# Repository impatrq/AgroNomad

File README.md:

<div align="center">
    
# [AgroNomad](https://linktr.ee/agronomad2026)

&nbsp;

| Página web | Linkedin | Instagram | Tiktok |
|------------|-------|-----------|---------|
|[AgroNomad Page](https://agro-nomad-page.vercel.app)|[AgroNomad](https://www.linkedin.com/company/145449198)|[@proyecto.agronomad](https://www.instagram.com/proyecto.agronomad/)|[@proyecto.agronomad](https://www.tiktok.com/@proyecto.agronomad)|

</div>

### MONITOREO INTELIGENTE DE GANADO 

AgroNomad es un sistema de monitoreo inteligente de ganado que combina collares smart, sensores, posicionamiento GPS y comunicación LoRa para obtener información de los animales directamente desde el campo.

El sistema está compuesto por collares inteligentes, una estación de recepción fija y una interfaz de usuario que permite visualizar y gestionar la información obtenida.

## Objetivo

Desarrollar un sistema IoT que permita realizar el seguimiento remoto del ganado, obteniendo información sobre su ubicación, movimiento y diferentes parámetros del animal, y centralizando estos datos en una estación de control.

## Componentes del Proyecto  

### AgroNeck

Collar inteligente colocado en el animal.

Se encarga de adquirir y procesar la información proveniente de los sensores y transmitirla mediante LoRa hacia el AgroBot.

### AgroBot

Estación de recepción fija del sistema.

Recibe la información enviada por los AgroNeck y funciona como centro de control para los animales monitoreados.

### AgroServer

Interfaz de usuario del sistema.

Permite visualizar y gestionar la información recibida desde los AgroNeck a través del AgroBot.

## Estructura del Proyecto  

| Ruta | Descripción |
|------------|---------|
|**docs**|Documentación e Informes del Proyecto|
|**firmware**|Software de los Microcontroladores y Aplicacion Web del Agrobot|
|**hardware**|Esquemáticos y PCB|
|**mechanical**|Diseños 3D|
|**web**|Landing Page del Proyecto|

---

<div align="center">

### AgroNeck  
<div style="margin-top:25px">

</div>

### AgroBot
<div style="margin-top:25px;">

</div>

</div>

## Equipo AgroNomad

<div align="center">
  
  <p><em>Equipo AgroNomad</em></p>
</div>

<br>

<div align="center">
  
  <p><em>Equipo AgroNomad en la Muestra Anual</em></p>
</div>

<br />

| Integrante | Rol | LinkedIn |
|------------|-----|----------|
| **Della Torre, Joaquín** | Diseño de placas electrónicas, montaje del AgroBot y desarrollo del AgroServer y Base de Datos. | [linkedin.com/in/joaquin-della-torre](https://www.linkedin.com/in/joaquin-della-torre/) |
| **Gonzalez Camiscia, Santiago** | Programación del AgroNeck, sistemas, optimización y gestión de energía con ESP32. | [linkedin.com/in/santiago-gonzalez](https://www.linkedin.com/in/santiago-gonzalez-a80209353/) |
| **Romero Dominguez, Braulio** | Diseño físico, desarrollo e integración del hardware y firmware y documentación. | [linkedin.com/in/braulio-romero-dominguez](www.linkedin.com/in/braulio-romero-dominguez-9a4729419) |
| **Villegas Gonzalez, Alejandro** | Desarrollo Web y de Interfaces. Programación e integración de datos. | [linkedin.com/in/alejandro-villegas-gonzalez](https://www.linkedin.com/in/alejandro-villegas-gonzalez-748a94432/) |

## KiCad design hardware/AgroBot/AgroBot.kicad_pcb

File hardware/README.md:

# Hardware

Esta carpeta contiene los diseños electrónicos del ecosistema AgroNomad desarrollados con KiCad. Incluye esquemáticos, placas PCB, proyectos de KiCad, vistas 3D y archivos de fabricación o impresión asociados a cada módulo.

El hardware se organiza en placas independientes según su función dentro del sistema:

- El **AgroBot** recibe los datos enviados por el AgroNeck.
- El **Cortex** constituye la lógica principal del collar AgroNeck.
- El **LoraShield**, el módulo MLX y el adaptador MOSFET son módulos auxiliares.
- El sistema **Solaria** administra la alimentación eléctrica mediante energía solar y baterías.

## Tipos de archivos

| Extensión | Descripción |
|---|---|
| `.kicad_sch` | Esquemático eléctrico: símbolos, conexiones y componentes de la placa. |
| `.kicad_pcb` | Diseño de la PCB: posición de componentes y trazado de pistas. |
| `.kicad_pro` | Archivo principal del proyecto de KiCad. |
| `.kicad_prl` | Configuración local de presentación o disposición del proyecto. |
| `*3D.png` | Vista renderizada del diseño tridimensional de la placa. |
| `*PCB.png` | Vista representativa del diseño o montaje de la PCB. |
| `fp-lib-table` / `sym-lib-table` | Tablas de bibliotecas locales de huellas y símbolos. |
| `libs/` | Bibliotecas, modelos 3D y recursos utilizados por el proyecto. |
| `gbr/` | Recursos relacionados con la preparación o trazado de fabricación. |

## Estructura

```text
hardware/
├── AgroBot/
├── Cortex/
├── LoraShield/
├── MLXModule/
├── MOSFETAdapter/
├── Solaria/
└── README.md
```

---

## AgroBot

El proyecto [`AgroBot/`](AgroBot/) corresponde a la estación de recepción fija del sistema.

**Función:** recibir la información emitida por los collares AgroNeck, determinar o conservar la ubicación mediante GPS y concentrar los datos para su procesamiento en el sistema principal.

<div align="center">
  
  <p><em>Diseño 3D del AgroBot</em></p>
</div>

El esquemático identifica una Raspberry Pi Zero 2 W como unidad de procesamiento, junto con módulos de comunicación LoRa y GPS.

| Archivo | Contenido |
|---|---|
| [`AgroBot.kicad_sch`](AgroBot/AgroBot.kicad_sch) | Esquemático del AgroBot. |
| [`AgroBot.kicad_pcb`](AgroBot/AgroBot.kicad_pcb) | Diseño físico y trazado de la PCB. |
| [`AgroBot.kicad_pro`](AgroBot/AgroBot.kicad_pro) | Proyecto de KiCad. |
| [`AgroBot3D.png`](AgroBot/AgroBot3D.png) | Representación tridimensional de la placa. |
| [`AgroBotPCB.png`](AgroBot/AgroBotPCB.png) | Vista de la PCB. |

---

## Cortex

El proyecto [`Cortex/`](Cortex/) representa la placa lógica principal del dispositivo AgroNeck, diseñado para instalarse dentro del collar inteligente.

**Función:** integrar el microcontrolador ESP32 con los módulos de comunicación y medición del collar. Procesa la información de posición y movimiento, comunica los datos por LoRa y gestiona las conexiones con los sensores.

<div align="center">
  
  <p><em>Diseño 3D de Cortex</em></p>
</div>

El esquemático contiene:

- ESP32 como unidad principal de procesamiento.
- Módulo GPS GY-NEO6MV2.
- Sensor MPU6050 para la detección de movimiento.
- Sensor MLX90614 para medición de temperatura.
- Interfaz de comunicación LoRa.
- Condensadores de desacoplo y conectores de alimentación o módulos auxiliares.

| Archivo | Contenido |
|---|---|
| [`Cortex.kicad_sch`](Cortex/Cortex.kicad_sch) | Esquemático de la lógica del AgroNeck. |
| [`Cortex.kicad_pcb`](Cortex/Cortex.kicad_pcb) | Diseño físico de la placa principal. |
| [`Cortex.kicad_pro`](Cortex/Cortex.kicad_pro) | Proyecto de KiCad. |
| [`Cortex3D.png`](Cortex/Cortex3D.png) | Vista tridimensional de Cortex. |
| [`CortexPCB.png`](Cortex/CortexPCB.png) | Vista de la PCB. |

---

## LoraShield

El proyecto [`LoraShield/`](LoraShield/) contiene una placa adaptadora basada en el módulo inalámbrico XL1278.

**Función:** proporcionar la interfaz física y eléctrica necesaria para conectar el módulo LoRa mediante conectores y facilitar su integración en el sistema.

<div align="center">
  
  <p><em>Diseño 3D del adaptador LoRa</em></p>
</div>

| Archivo | Contenido |
|---|---|
| [`LoraShield.kicad_sch`](LoraShield/LoraShield.kicad_sch) | Esquemático del adaptador LoRa. |
| [`LoraShield.kicad_pcb`](LoraShield/LoraShield.kicad_pcb) | Diseño físico de la placa. |
| [`LoraShield.kicad_pro`](LoraShield/LoraShield.kicad_pro) | Proyecto de KiCad. |
| [`LoraShield3D.png`](LoraShield/LoraShield3D.png) | Vista tridimensional del módulo. |
| [`LoraShieldPCB.png`](LoraShield/LoraShieldPCB.png) | Vista de la PCB. |

---

## MLXModule

El proyecto [`MLXModule/`](MLXModule/) corresponde a una placa auxiliar diseñada para el sensor infrarrojo de temperatura MLX90614.

**Función:** montar y conectar el sensor MLX90614 mediante un conector de cuatro posiciones, permitiendo llevar las señales de alimentación y comunicación entre el módulo y la placa Cortex.

<div align="center">
  
  <p><em>Módulo auxiliar del sensor MLX90614</em></p>
</div>

| Archivo | Contenido |
|---|---|
| [`MLXModule.kicad_sch`](MLXModule/MLXModule.kicad_sch) | Esquemático del módulo MLX90614. |
| [`MLXModule.kicad_pcb`](MLXModule/MLXModule.kicad_pcb) | Diseño físico de la placa auxiliar. |
| [`MLXModule.kicad_pro`](MLXModule/MLXModule.kicad_pro) | Proyecto de KiCad. |
| [`MLXModule3D.png`](MLXModule/MLXModule3D.png) | Vista tridimensional del módulo. |
| [`MLXModulePCB.png`](MLXModule/MLXModulePCB.png) | Vista de la PCB. |

---

## MOSFETAdapter

El proyecto [`MOSFETAdapter/`](MOSFETAdapter/) reúne un adaptador para trabajar con MOSFET en paquetes THT y SMD.

**Función:** facilitar el montaje y reemplazo de MOSFET en prototipos o placas donde se necesita compatibilidad entre formatos de componentes.

El diseño incluye los modelos **AO3401A** y **IRF9540N**, utilizados como dispositivos MOSFET en el proyecto.

| Archivo | Contenido |
|---|---|
| [`Adapter.kicad_sch`](MOSFETAdapter/Adapter.kicad_sch) | Esquemático del adaptador. |
| [`Adapter.kicad_pcb`](MOSFETAdapter/Adapter.kicad_pcb) | Diseño físico de la PCB. |
| [`Adapter.kicad_pro`](MOSFETAdapter/Adapter.kicad_pro) | Proyecto de KiCad. |
| [`Adapter3D.png`](MOSFETAdapter/Adapter3D.png) | Vista tridimensional del adaptador. |
| [`AdapterPCB.png`](MOSFETAdapter/AdapterPCB.png) | Vista de la PCB. |

---

## Solaria

El proyecto [`Solaria/`](Solaria/) corresponde al sistema electrónico de alimentación solar.

**Función:** administrar la energía captada por paneles solares, cargar baterías y elevar o distribuir la tensión necesaria para alimentar los dispositivos del sistema.

<div align="center">
  
  <p><em>Diseño 3D del sistema de alimentación</em></p>
</div>

El esquemático utiliza módulos TP4056 para la carga y gestión de baterías, junto con un conversor elevador MT3608 y MOSFET de potencia. La PCB incluye entradas y conexiones para panel solar, batería y carga.

| Archivo | Contenido |
|---|---|
| [`Solaria.kicad_sch`](Solaria/Solaria.kicad_sch) | Esquemático del sistema de alimentación. |
| [`Solaria.kicad_pcb`](Solaria/Solaria.kicad_pcb) | Diseño físico de la PCB. |
| [`Solaria.kicad_pro`](Solaria/Solaria.kicad_pro) | Proyecto de KiCad. |
| [`Solaria3D.png`](Solaria/Solaria3D.png) | Vista tridimensional de la placa. |
| [`SolariaPCB.png`](Solaria/SolariaPCB.png) | Vista de la PCB. |

## Abrir los diseños

1. Instalar una versión de KiCad compatible con los archivos del proyecto.
2. Abrir el archivo `.kicad_pro` correspondiente a la placa.
3. Desde el proyecto abrir `.kicad_sch` para revisar el circuito o `.kicad_pcb` para revisar el diseño físico.
4. Verificar las bibliotecas locales y los modelos 3D incluidos en `libs/` antes de modificar o exportar el diseño.

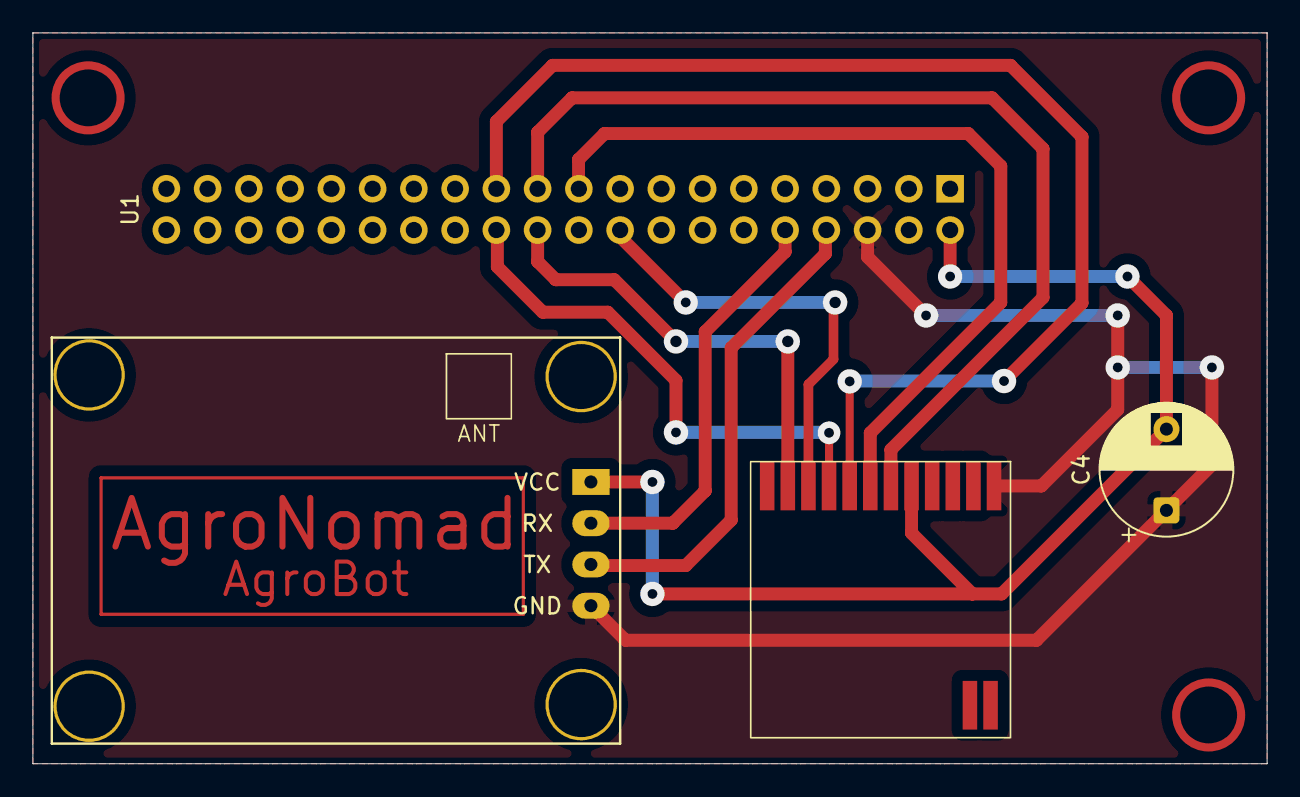
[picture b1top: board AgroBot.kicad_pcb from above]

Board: 2 copper layers, 76.0 x 45.0 mm, 4 parts (0 on the bottom side), 10 nets.

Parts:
C4: 100uF; CP_Radial_D8.0mm_P5.00mm
U1: Pi Zero 2 W; PinHeader_2x20_P2.54mm_Vertical
U2: XL1278
U3: GY-NEO6MV2

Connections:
GND: C4.1, U1.6 (GND), U2.1 (GND), U3.4 (GND)
GPS_RX: U1.10 (GPIO15), U3.2 (RX)
GPS_TX: U1.8 (GPIO14), U3.3 (TX)
LORA_CLK: U1.23 (GPIO11), U2.8 (SCLK)
LORA_CS: U1.24 (GPIO8), U2.9 (NSS)
LORA_DIO0: U1.18 (GPIO24), U2.10 (DIO0)
LORA_MISO: U1.21 (GPIO09), U2.6 (MISO)
LORA_MOSI: U1.19 (GPIO10), U2.7 (MOSI)
LORA_RESET: U1.22 (GPIO25), U2.11 (REST)
VCC: C4.2, U1.2 (+5V), U2.5 (VCC), U3.1 (VCC)

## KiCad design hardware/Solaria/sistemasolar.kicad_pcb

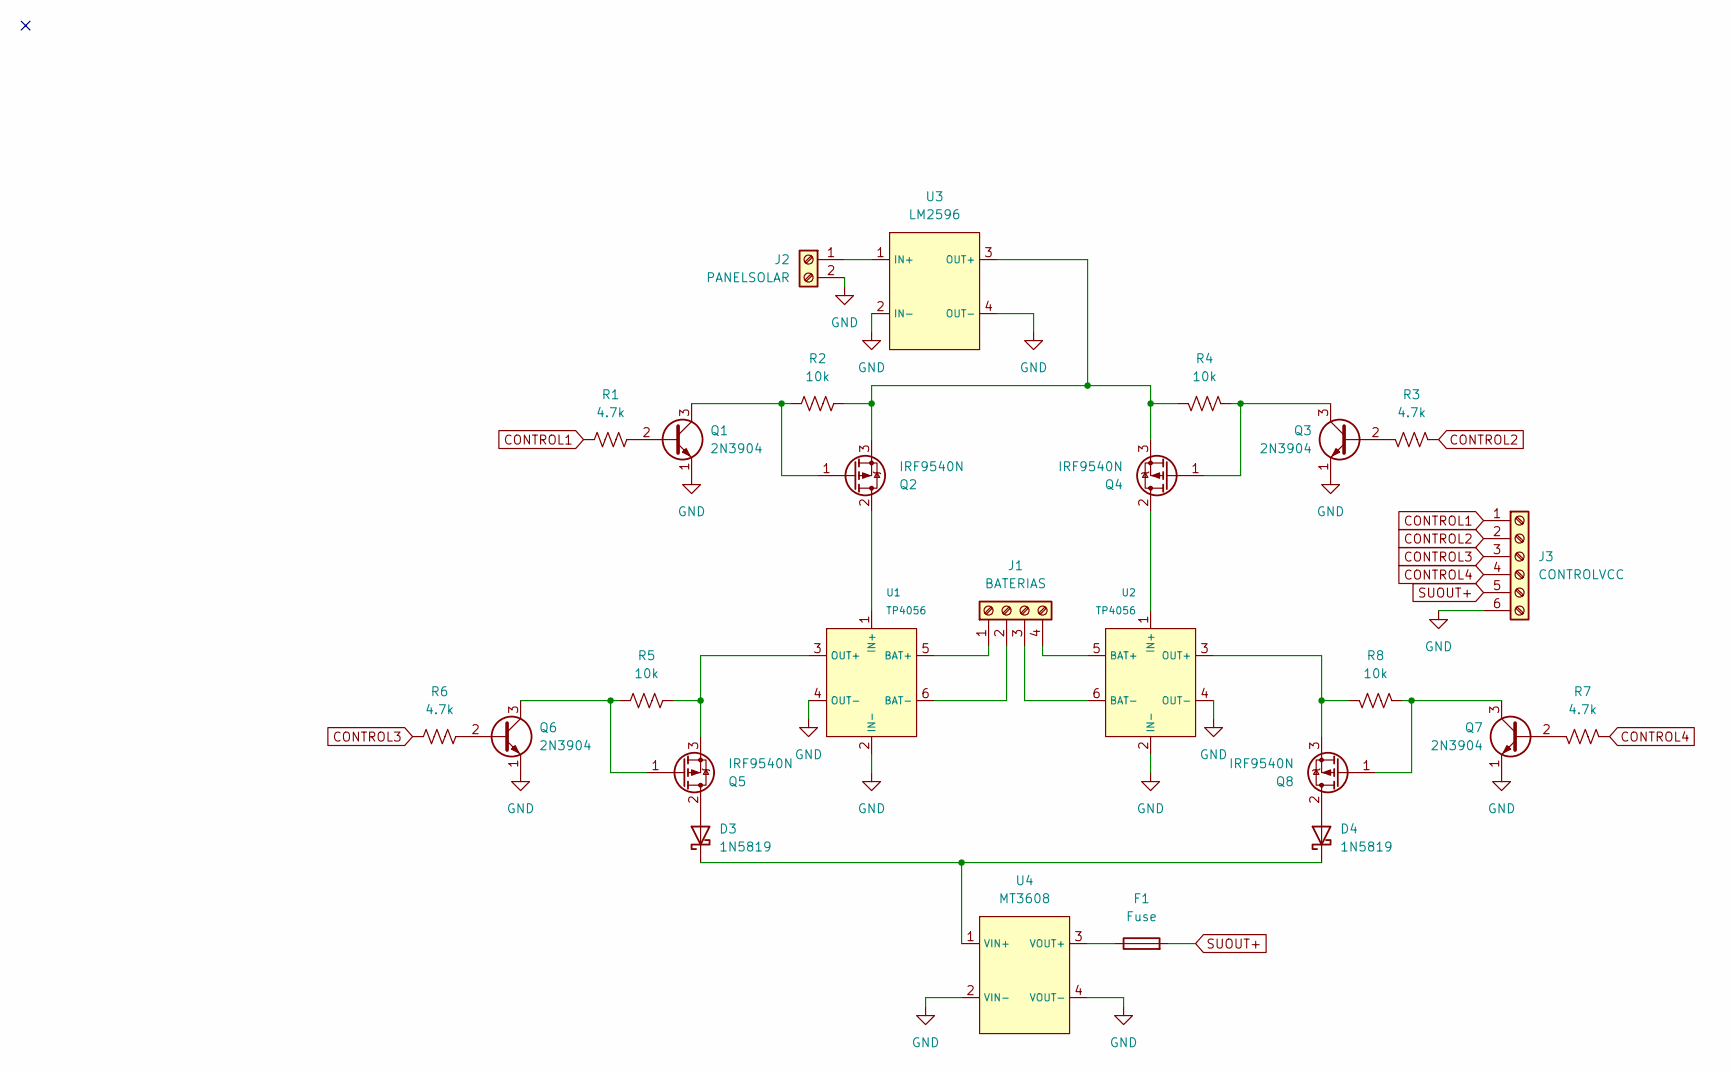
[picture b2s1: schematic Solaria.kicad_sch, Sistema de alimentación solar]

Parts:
D3, D4: 1N5819; D_DO-41_SOD81_P10.16mm_Horizontal
F1: Fuse; Fuseholder_Clip-5x20mm_Littelfuse_445-030_Inline_P20.50x5.2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
J1: BATERIAS; TerminalBlock_MaiXu_MX126-5.0-04P_1x04_P5.00mm
J2: PANELSOLAR; TerminalBlock_MaiXu_MX126-5.0-02P_1x02_P5.00mm
J3: CONTROLVCC; TerminalBlock_MaiXu_MX126-5.0-06P_1x06_P5.00mm
Q1, Q3, Q6, Q7: 2N3904; TO-92_Inline
Q2, Q4, Q5, Q8: IRF9540N; TO-220-3_Vertical
R1, R3, R6, R7: 4.7k; R_Axial_DIN0204_L3.6mm_D1.6mm_P7.62mm_Horizontal
R2, R4, R5, R8: 10k; R_Axial_DIN0204_L3.6mm_D1.6mm_P7.62mm_Horizontal
U1, U2: TP4056
U3: LM2596
U4: MT3608

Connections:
CONTROL1: J3.1, R1.1
CONTROL2: J3.2, R3.1
CONTROL3: J3.3, R6.1
CONTROL4: J3.4, R7.1
GND: J2.2, J3.6, Q1.1 (E), Q3.1 (E), Q6.1 (E), Q7.1 (E), U1.2 (IN-), U1.4 (OUT-), U2.2 (IN-), U2.4 (OUT-), U3.2 (IN-), U3.4 (OUT-), U4.2 (VIN-), U4.4 (VOUT-)
unnamed: D3.2 (A), Q5.2 (D)
unnamed: D3.1 (K), D4.1 (K), U4.1 (VIN+)
unnamed: D4.2 (A), Q8.2 (D)
unnamed: J1.1, U1.5 (BAT+)
unnamed: J1.2, U1.6 (BAT-)
unnamed: J1.3, U2.6 (BAT-)
unnamed: J1.4, U2.5 (BAT+)
unnamed: J2.1, U3.1 (IN+)
unnamed: Q1.2 (B), R1.2
unnamed: Q1.3 (C), Q2.1 (G), R2.1
unnamed: Q2.2 (D), U1.1 (IN+)
unnamed: Q2.3 (S), Q4.3 (S), R2.2, R4.2, U3.3 (OUT+)
unnamed: Q3.2 (B), R3.2
unnamed: Q3.3 (C), Q4.1 (G), R4.1
unnamed: Q4.2 (D), U2.1 (IN+)
unnamed: Q5.1 (G), Q6.3 (C), R5.1
unnamed: Q5.3 (S), R5.2, U1.3 (OUT+)
unnamed: Q6.2 (B), R6.2
unnamed: Q7.2 (B), R7.2
unnamed: Q7.3 (C), Q8.1 (G), R8.1
unnamed: Q8.3 (S), R8.2, U2.3 (OUT+)
unnamed: F1.1, U4.3 (VOUT+)
SUOUT+: F1.2, J3.5

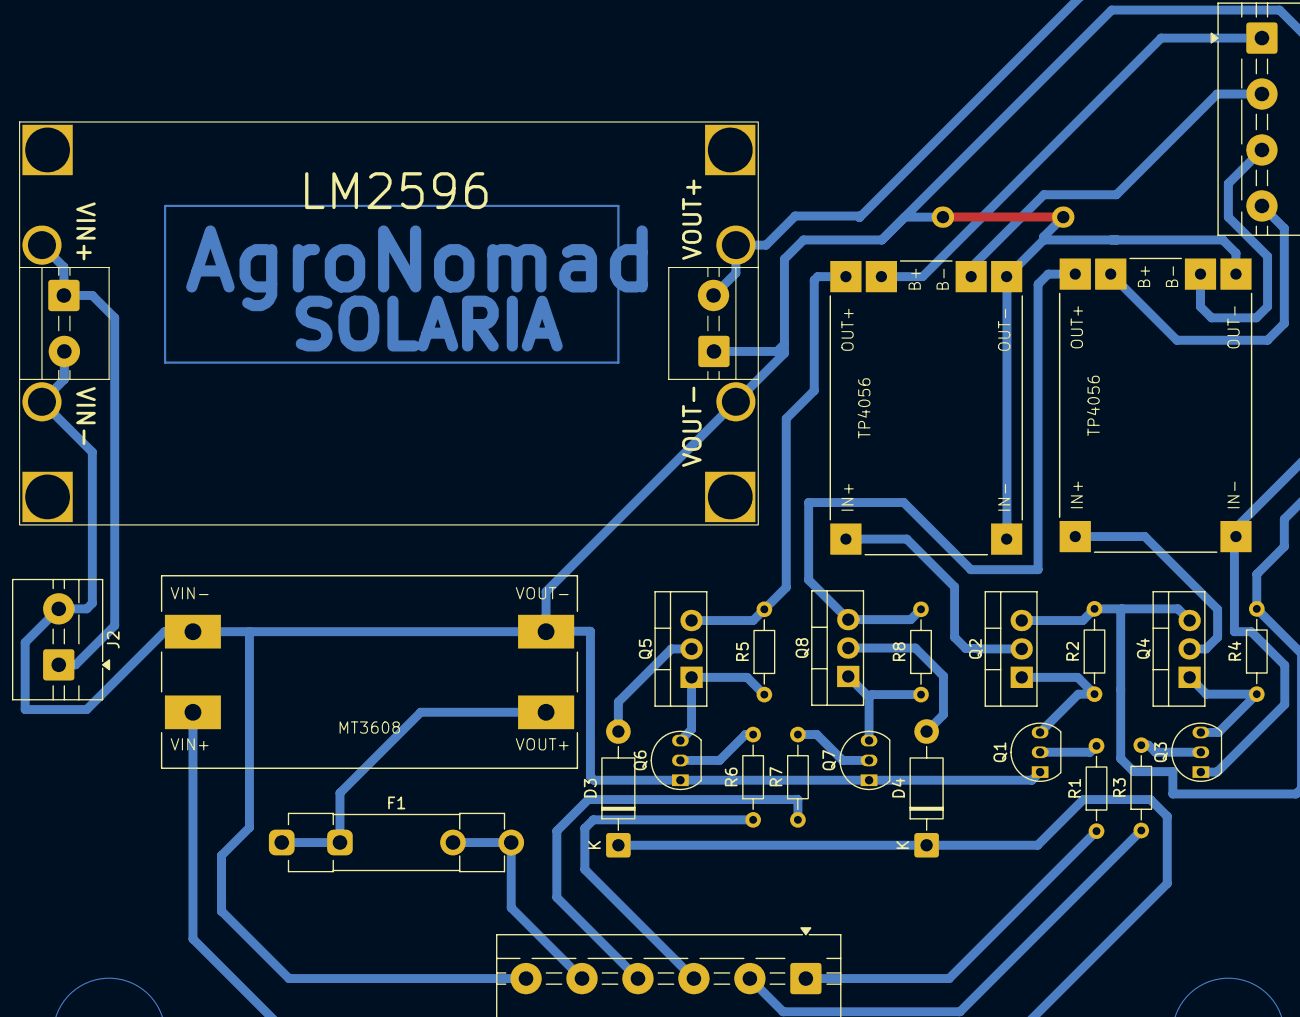
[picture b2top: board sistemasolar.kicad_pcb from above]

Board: 2 copper layers, 26 parts (0 on the bottom side), 28 nets.

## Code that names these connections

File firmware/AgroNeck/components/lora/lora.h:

#include <stdint.h>
#include <stdbool.h>

// Pines LORA
#define LORA_CS         5
#define LORA_RESET      14
#define LORA_CLK        18
#define LORA_MISO       19
#define LORA_MOSI       23
#define LORA_DIO0       10

// Estructuras
typedef struct __attribute__((packed)) {
    uint16_t id_collar;
    float temperatura;     
    int32_t latitud;       
    int32_t longitud;     
} payload_t;               

// Funciones
void lora_init(void);
void lora_reinit(void);
void transmitir_datos(payload_t *paquete);
uint8_t lora_version(void);   // diagnóstico: lee el registro de versión (0x42)

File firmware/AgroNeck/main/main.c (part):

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#define SEND_EVERYTIME 1

// CONTROL DE ALIMENTACIÓN - C1+C4 o C2+C3
#define MOSFET1 25 // GPIO del MOSFET CONTROL3
#define MOSFET2 26 // GPIO del MOSFET CONTROL4
#define MOSFET3 32 // GPIO del MOSFET CONTROL1
#define MOSFET4 33 // GPIO del MOSFET CONTROL2

// Mascara de manejo de los 4 pines
#define GPIO_MOSFET_MASK ((1ULL<<MOSFET1) | (1ULL<<MOSFET2) | (1ULL<<MOSFET3) | (1ULL<<MOSFET4))
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
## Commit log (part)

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2026-04-08 Anteproyecto uploaded
2026-04-08 docs readme updated
2026-04-08 created dir for docs
2026-06-03 feat(solaria): proyecto inicial de KiCad de placa de alimentación solar
    esquemático, pcb y modelo 3d de la placa
2026-06-16 added hardware directory with PCB developed until 15/6
